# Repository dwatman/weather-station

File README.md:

# weather-station

Weather station with precision sensors, ZigBee connectivity to Home Assistant.

## Wireless Module
STM32WBA5MMG Wireless Module

## Sensors

| Type         | Part           | Accuracy          | Interface   | Voltage       | Current | Response |
| ------------ | -------------- | ----------------- | ----------- | ------------- | ------- | -------- |
| Temperature  | SHT45-AD1F | ± 0.1°C           | I²C         | 1.08 - 3.6 V  | 0.4 uA  | 4 s      |
| Humidity     | SHT45-AD1F | ± 1% RH           | I²C         | 1.08 - 3.6 V  | 0.4 uA  | 4 s      |
| Pressure     | LPS22DF    | ± 0.2 hPa         | I²C/SPI/I3C | 1.7 - 3.6 V   | 9 uA    | fast     |
| CO₂          | SCD41      | ±50.0 ppm + 2.5 % | I²C         | 2.4 - 5.5 V   | 15 mA   | 60 s     |
| VOC + NOx    | SGP41      | ± 15%?            | I²C         | 1.7 - 3.6 V   | 3 mA    | 10 s     |
| Particles    | SPS30      | ± 10%             | I²C/UART    | 4.5 - 5.5 V   | 55 mA   |          |
| Light        | OPT4001    | ± 2%              | I²C         | 1.6 - 3.6 V   | 30 µA   | <0.8 s   |
| Sound        | ICS-43434  | ± ?dB             | I²S         | 1.65 - 3.63 V | 490 µA  |          |
| Acceleration | LIS2HH12   | ± 0.1%            | I²C/SPI     | 1.71 - 3.6 V  | 180 µA  |          |
| IR Rx        | TSOP38436  | N/A               | Digital     | 2.0 - 5.5 V   | 450 µA  |          |

## Indoor Sensor Unit
* ZigBee for communication
* USB powered

### Sensors
* Temperature
* Humidity
* CO2
* VOC + NOx
* Particles
* Light
* IR remote control

## Outdoor Sensor Unit
* ZigBee for communication
* Solar + battery powered
* ~0.5 - 1W solar panel
* 18650 lithium cell for energy storage
* BQ25570 for solar/charge control

### Sensors
* Temperature
* Humidity
* Pressure
* Light (+UV?)
* Sound
* Battery level

## Display Unit
* WiFi for communication
* STM32H???

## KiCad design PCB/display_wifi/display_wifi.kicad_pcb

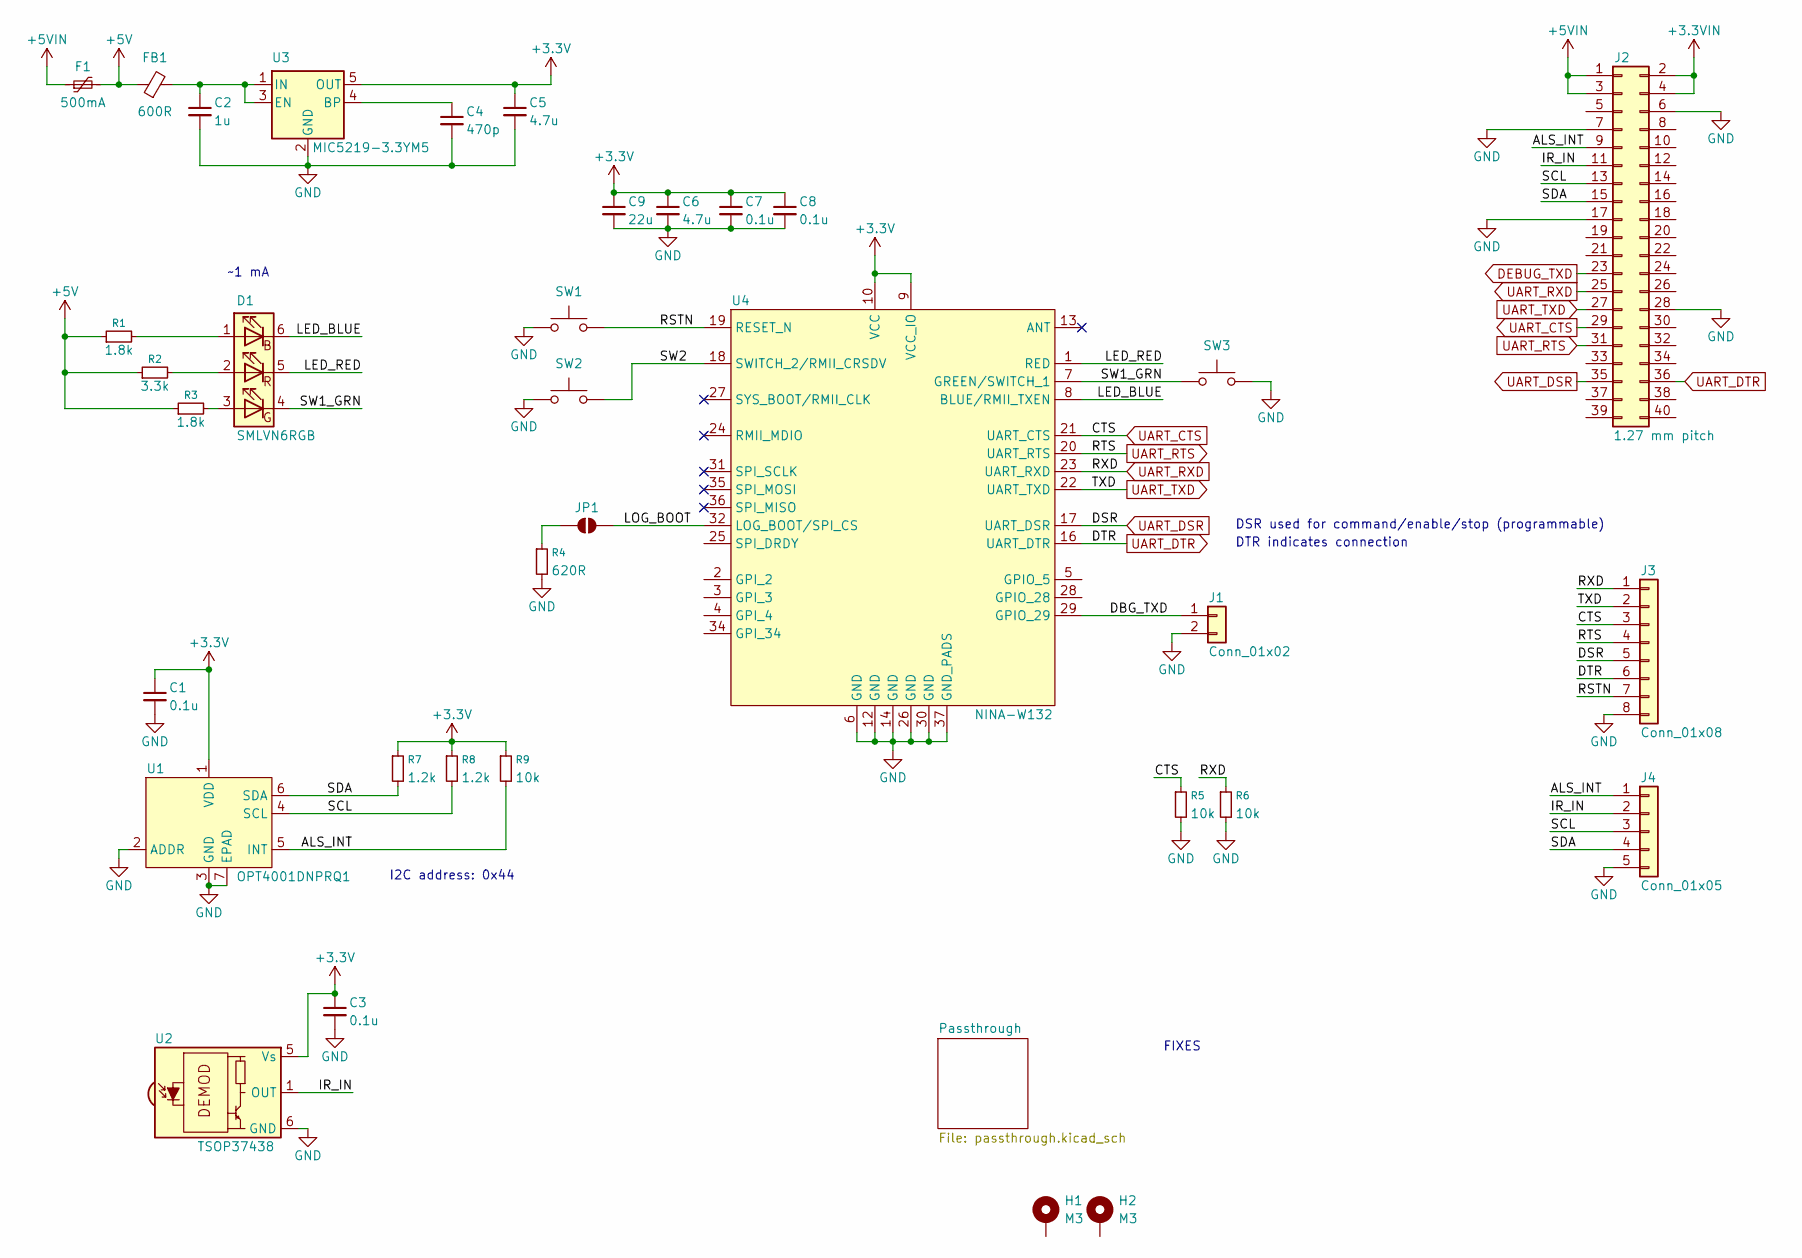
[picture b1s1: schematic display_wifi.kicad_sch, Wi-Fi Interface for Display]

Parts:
C1, C3, C7, C8: 0.1u; C_0402_1005Metric; MPN CL05B104KA5NNNC; Mouser PN 187-CL05B104KA5NNNC
C2: 1u; C_0402_1005Metric; MPN CL05A105KA5NQNC; Mouser PN 187-CL05A105KA5NQNC
C4: 470p; C_0402_1005Metric; MPN GRM1555C2A471JE01D; Mouser PN 81-GRM1555C2A471JE1D
C5, C6: 4.7u; C_0603_1608Metric; MPN CL10A475KO8NNNC; Mouser PN 187-CL10A475KO8NNNC
C9: 22u; C_1210_3225Metric
D1: SMLVN6RGB; LED_ROHM_SMLVN6; MPN SMLVN6RGB7W1; Mouser PN 755-SMLVN6RGB7W1
F1: 500mA; Fuse_1206_3216Metric; MPN MF-NSMF050-2; Mouser PN 652-MF-NSMF050-2
FB1: 600R; L_0805_2012Metric; MPN BLM21SP601SZ1D; Mouser PN 81-BLM21SP601SZ1D
H1, H2: M3; MountingHole_3.2mm_M3_Pad
J1: Conn_01x02; PinHeader_1x02_P2.54mm_Vertical
J2: 1.27 mm pitch; PinSocket_2x20_P1.27mm_Vertical; MPN 20021311-00040T4LF; Mouser PN 649-221311-00040T4LF
J3: Conn_01x08; PinHeader_1x08_P2.54mm_Vertical
J4: Conn_01x05; PinHeader_1x05_P2.54mm_Vertical
JP1: SolderJumper_2_Open; SolderJumper-2_P1.3mm_Open_TrianglePad1.0x1.5mm
R1, R3: 1.8k; R_0603_1608Metric
R2: 3.3k; R_0603_1608Metric
R4: 620R; R_0603_1608Metric
R5, R6, R9: 10k; R_0603_1608Metric
R7, R8: 1.2k; R_0603_1608Metric
SW1, SW2, SW3: TL3305; SW_Push_1P1T_NO_E-Switch_TL3305AFxxxQG; MPN TL3305BF100QG; Mouser PN 612-TL3305BF100QG
U1: OPT4001DNPRQ1; TI_USON-6-1EP_2x2mm_P0.5mm_EP0.65x1.35mm; MPN OPT4001DNPRQ1; Mouser PN 595-OPT4001DNPRQ1
U2: TSOP37438; Vishay_BELOBOG-4Pin; MPN TSOP37438TT1; Mouser PN 78-TSOP37438TT1
U3: MIC5219-3.3YM5; SOT-23-5; MPN MIC5219-3.3YM5-TR; Mouser PN 998-MIC5219-3.3YM5TR
U4: NINA-W132; ublox_NINA-W1x2; MPN NINA-W132-03B; Mouser PN 377-NINA-W132-03B

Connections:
+3.3V: C1.1, C3.1, C5.1, C6.1, C7.1, C8.1, C9.1, R7.1, R8.1, R9.1, U1.1 (VDD), U2.5 (Vs), U3.5 (OUT), U4.9 (VCC_IO), U4.10 (VCC)
+3.3VIN: J2.2, J2.4
+5V: F1.2, FB1.1, R1.1, R2.1, R3.1
+5VIN: F1.1, J2.1, J2.3
/ALS_INT: J2.9, J4.1, R9.2, U1.5 (INT)
/DBG_TXD: J1.1, U4.29 (GPIO_29)
/IR_IN: J2.11, J4.2, U2.1 (OUT)
/LED_BLUE: D1.6 (BK), U4.8 (BLUE/RMII_TXEN)
/LED_RED: D1.5 (RK), U4.1 (RED)
/LOG_BOOT: JP1.2 (B), U4.32 (LOG_BOOT/SPI_CS)
/RSTN: J3.7, SW1.2, U4.19 (RESET_N)
/SCL: J2.13, J4.3, R8.2, U1.4 (SCL)
/SDA: J2.15, J4.4, R7.2, U1.6 (SDA)
/SW1_GRN: D1.4 (GK), SW3.1, U4.7 (GREEN/SWITCH_1)
/SW2: SW2.2, U4.18 (SWITCH_2/RMII_CRSDV)
DEBUG_TXD: J2.23; also elsewhere on the board
GND: C1.2, C2.2, C3.2, C4.2, C5.2, C6.2, C7.2, C8.2, C9.2, J1.2, J2.6, J2.7, J2.17, J2.28, J3.8, J4.5, R4.2, R5.2, R6.2, SW1.1, SW2.1, SW3.2, U1.2 (ADDR), U1.3 (GND), U1.7 (EPAD), U2.6 (GND), U2.8 (GND), U3.2 (GND), U4.6 (GND), U4.12 (GND), U4.14 (GND), U4.26 (GND), U4.30 (GND), U4.37 (GND_PADS); also elsewhere on the board
unnamed: D1.1 (BA), R1.2
unnamed: D1.3 (GA), R3.2
unnamed: D1.2 (RA), R2.2
unnamed: JP1.1 (A), R4.1
unnamed: C4.1, U3.4 (BP)
unnamed: C2.1, FB1.2, U3.1 (IN), U3.3 (EN)
UART_CTS: J2.29, J3.3, R5.1, U4.21 (UART_CTS)
UART_DSR: J2.35, J3.5, U4.17 (UART_DSR)
UART_DTR: J2.36, J3.6, U4.16 (UART_DTR)
UART_RTS: J2.31, J3.4, U4.20 (UART_RTS)
UART_RXD: J2.25, J3.1, R6.1, U4.23 (UART_RXD)
UART_TXD: J2.27, J3.2, U4.22 (UART_TXD)

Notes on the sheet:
DTR indicates connection
DSR used for command/enable/stop (programmable)
I2C address: 0x44
~1 mA
FIXES

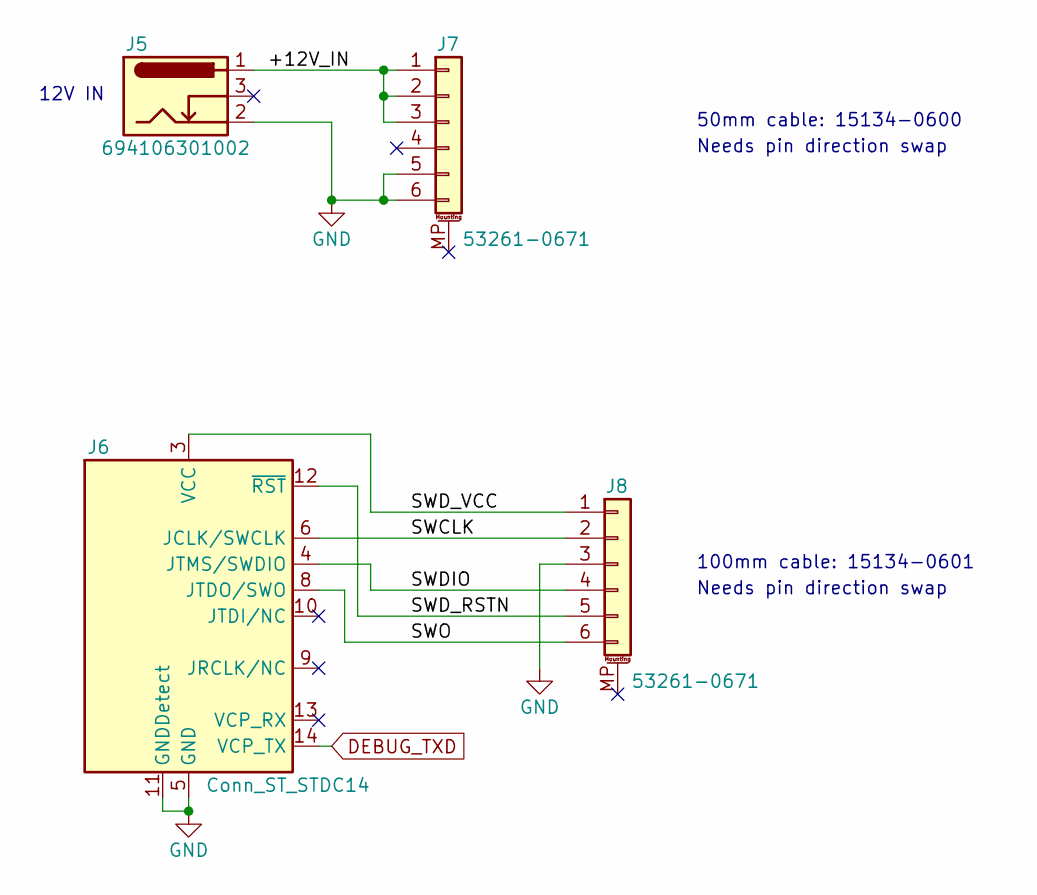
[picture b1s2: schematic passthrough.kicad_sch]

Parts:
J5: 694106301002; BarrelJack_Wuerth_6941xx301002; MPN 694106301002; Mouser PN 710-694106301002
J6: Conn_ST_STDC14; PinHeader_2x07_P1.27mm_Vertical; MPN 20021111-00014T1LF; Mouser PN 649-200211110014T1LF
J7, J8: 53261-0671; Molex_PicoBlade_53261-0671_1x06-1MP_P1.25mm_Horizontal; MPN 53261-0671; Mouser PN 538-53261-0671

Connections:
/Passthrough/+12V_IN: J5.1, J7.1, J7.2, J7.3
/Passthrough/SWCLK: J6.6 (JCLK/SWCLK), J8.2
/Passthrough/SWDIO: J6.4 (JTMS/SWDIO), J8.4
/Passthrough/SWD_RSTN: J6.12 (~RST), J8.5
/Passthrough/SWD_VCC: J6.3 (VCC), J8.1
/Passthrough/SWO: J6.8 (JTDO/SWO), J8.6
DEBUG_TXD: J6.14 (VCP_TX); also elsewhere on the board
GND: J5.2, J6.5 (GND), J6.7 (GND), J6.11 (GNDDetect), J7.5, J7.6, J8.3; also elsewhere on the board

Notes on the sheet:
50mm cable: 15134-0600
Needs pin direction swap
100mm cable: 15134-0601
12V IN

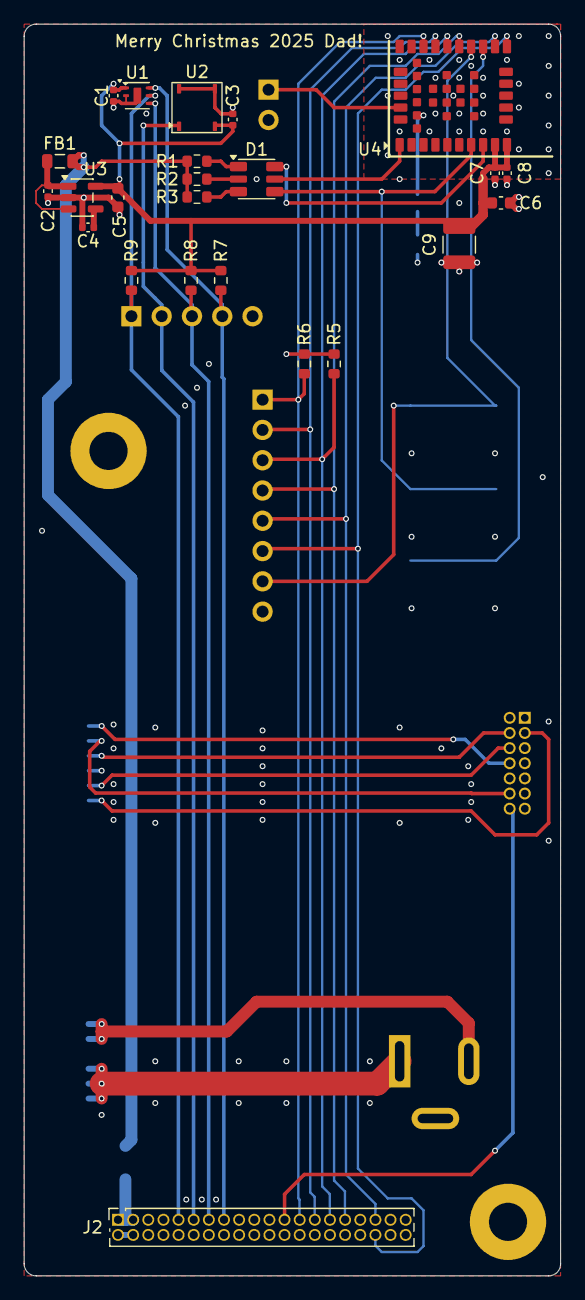
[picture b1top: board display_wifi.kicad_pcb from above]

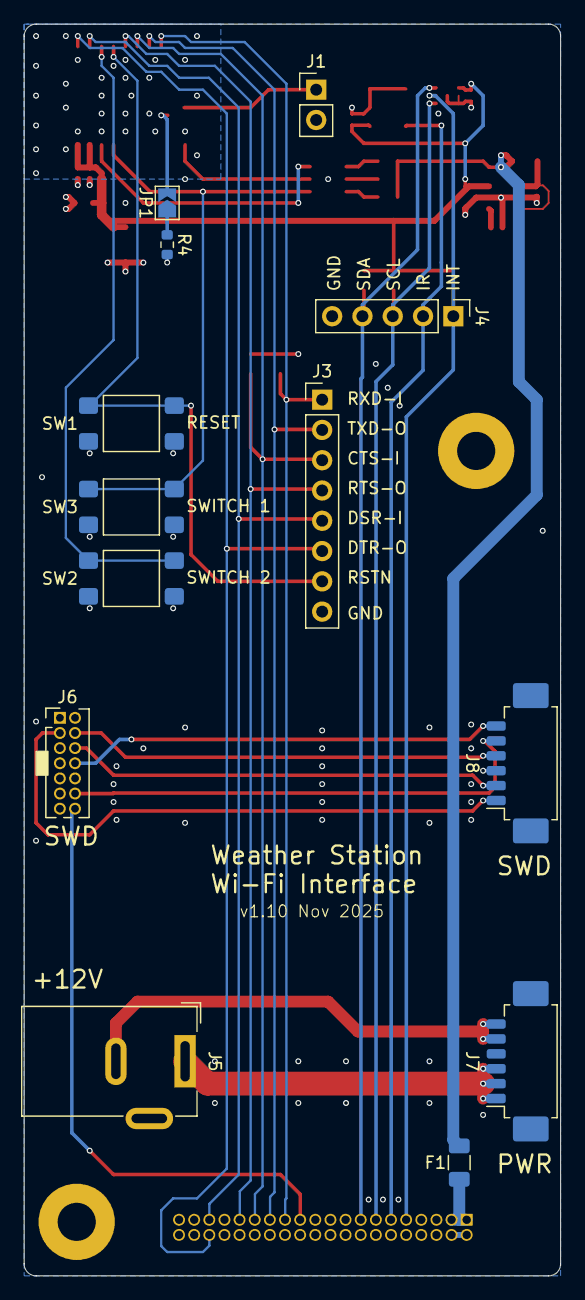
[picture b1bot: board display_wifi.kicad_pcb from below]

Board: 2 copper layers, 45.0 x 105.0 mm, 39 parts (13 on the bottom side), 35 nets.

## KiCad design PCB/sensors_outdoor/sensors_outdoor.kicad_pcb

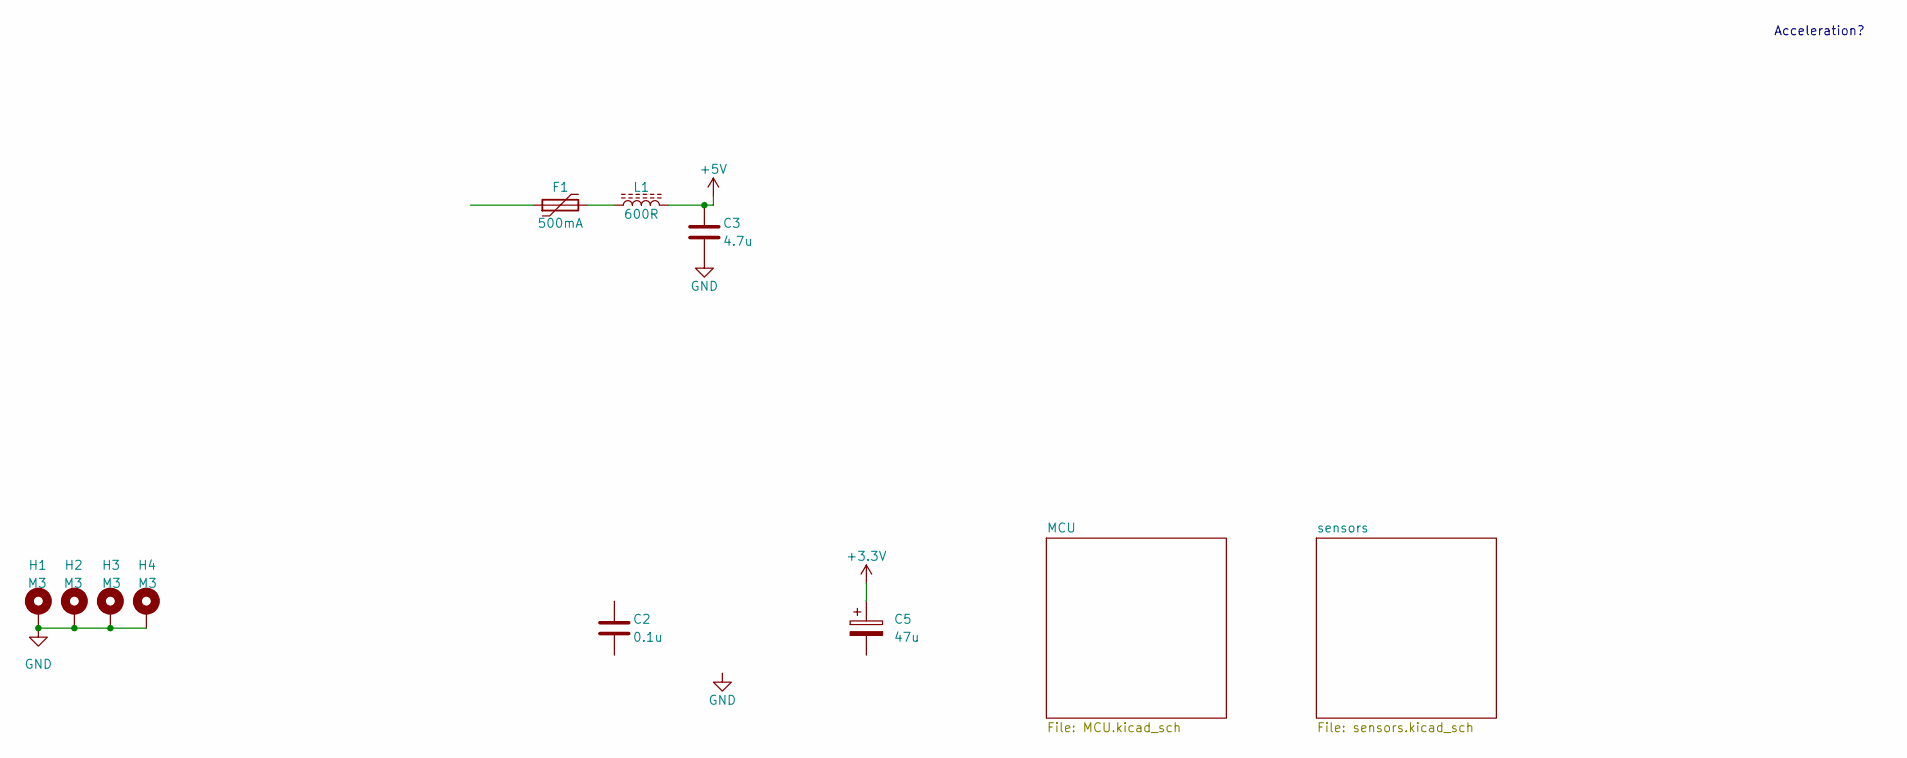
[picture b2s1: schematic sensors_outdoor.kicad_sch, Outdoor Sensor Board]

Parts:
C2: 0.1u; C_0402_1005Metric
C3: 4.7u; C_0805_2012Metric
C5: 47u; CP_EIA-7343-31_Kemet-D; MPN T491D476K010AT; Mouser PN 80-T491D476K010
F1: 500mA; Fuse_0805_2012Metric
H1, H2, H3, H4: M3; MountingHole_3.2mm_M3_Pad
L1: 600R; L_0805_2012Metric; MPN HZ0805E601R-10; Mouser PN 875-HZ0805E601R-10

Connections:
+3.3V: C5.1; also elsewhere on the board
+5V: C3.1, L1.2
GND: C3.2, H1.1, H2.1, H3.1, H4.1; also elsewhere on the board
unnamed: F1.2, L1.1

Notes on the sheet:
Acceleration?

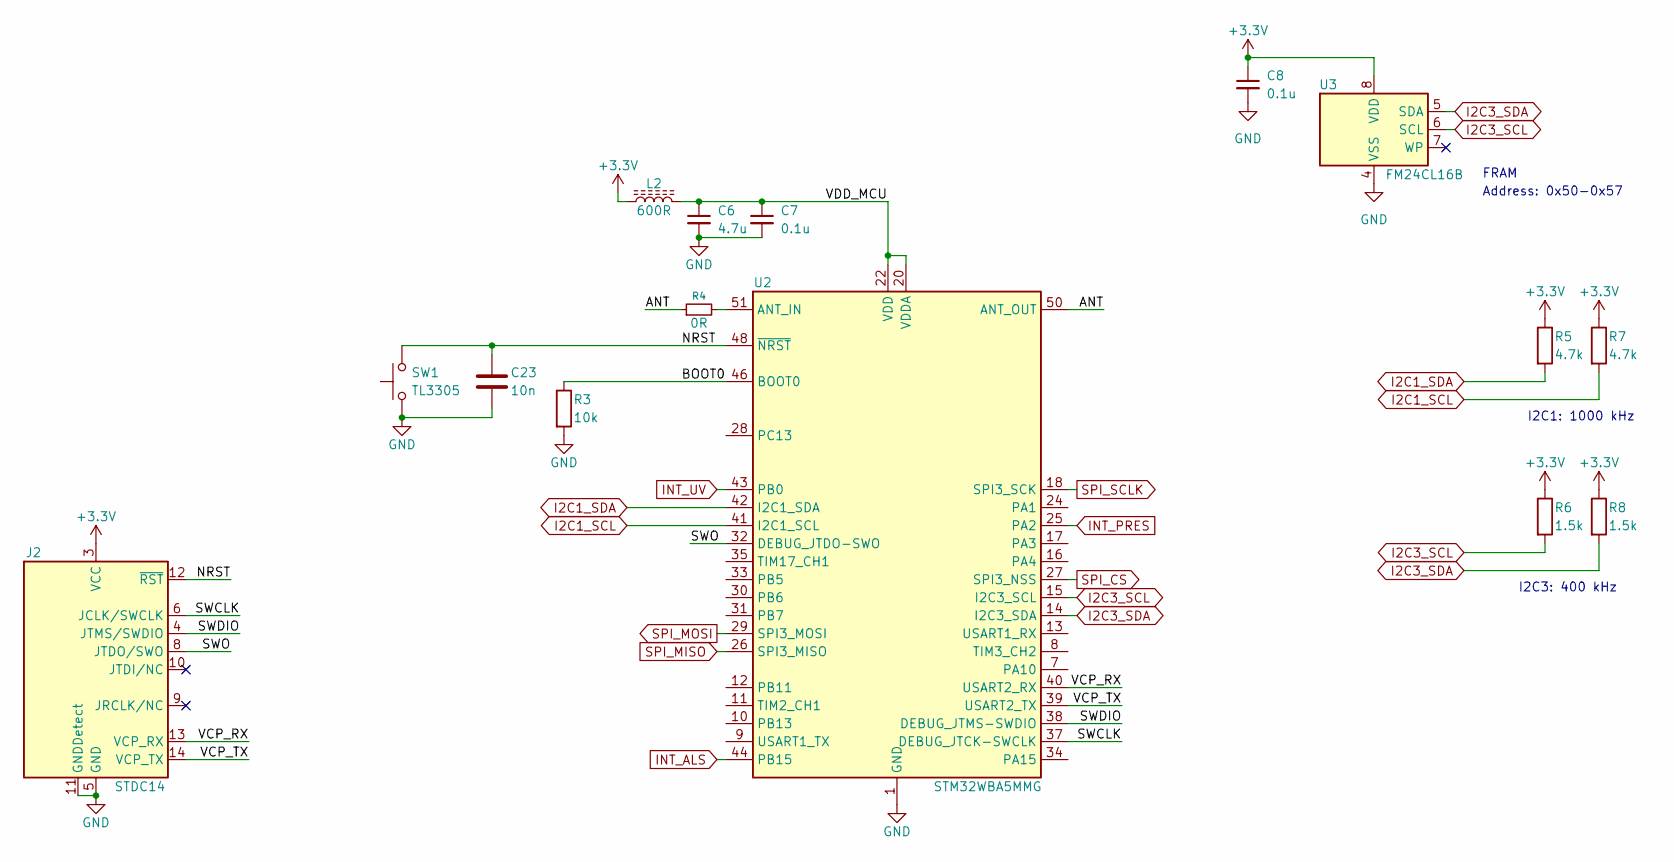
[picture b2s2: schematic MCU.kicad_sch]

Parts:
C6: 4.7u; C_0805_2012Metric
C7, C8: 0.1u; C_0402_1005Metric
C23: 10n; C_0402_1005Metric
J2: STDC14; SAMTEC_FTSH-107-01-L-DV-K-A; MPN FTSH-107-01-L-DV-K-A; Mouser PN 200-FTSH10701LDVKA
L2: 600R; L_0805_2012Metric; MPN HZ0805E601R-10; Mouser PN 875-HZ0805E601R-10
R3: 10k; R_0603_1608Metric
R4: 0R; R_0402_1005Metric
R5, R7: 4.7k; R_0603_1608Metric
R6, R8: 1.5k; R_0603_1608Metric
SW1: TL3305; SW_Push_1P1T_NO_E-Switch_TL3305AFxxxQG; MPN TL3305AF260QG; Mouser PN 612-TL3305AF260QG
U2: STM32WBA5MMG; MPN STM32WBA5MMGH6TR; Mouser PN 511-STM32WBA5MMGH6TR
U3: FM24CL16B; SOIC-8_3.9x4.9mm_P1.27mm; MPN FM24CL16B-G; Mouser PN 877-FM24CL16B-G

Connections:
+3.3V: C8.1, J2.3 (VCC), L2.1, R5.1, R6.1, R7.1, R8.1, U3.8 (VDD); also elsewhere on the board
/MCU/ANT: R4.1, U2.50 (ANT_OUT)
/MCU/BOOT0: R3.1, U2.46 (BOOT0)
/MCU/NRST: C23.1, J2.12 (~RST), SW1.2, U2.48 (~NRST)
/MCU/SWCLK: J2.6 (JCLK/SWCLK), U2.37 (DEBUG_JTCK-SWCLK)
/MCU/SWDIO: J2.4 (JTMS/SWDIO), U2.38 (DEBUG_JTMS-SWDIO)
/MCU/SWO: J2.8 (JTDO/SWO), U2.32 (DEBUG_JTDO-SWO)
/MCU/VCP_RX: J2.13 (VCP_RX), U2.40 (USART2_RX)
/MCU/VCP_TX: J2.14 (VCP_TX), U2.39 (USART2_TX)
/MCU/VDD_MCU: C6.1, C7.1, L2.2, U2.20 (VDDA), U2.22 (VDD)
GND: C6.2, C7.2, C8.2, C23.2, J2.5 (GND), J2.7 (GND), J2.11 (GNDDetect), R3.2, SW1.1, U2.1 (GND), U2.6 (GND), U2.19 (GND), U2.21 (GND), U2.23 (GND), U2.36 (GND), U2.45 (GND), U2.47 (GND), U2.49 (GND), U2.52 (GND), U2.53 (GND), U2.54 (GND), U2.55 (GND), U2.57 (GND), U2.58 (GND), U2.60 (GND), U2.61 (GND), U2.62 (GND), U2.63 (GND), U2.64 (GND), U2.65 (GND), U2.66 (GND), U2.67 (GND), U2.68 (GND), U2.69 (GND), U2.70 (GND), U2.71 (GND), U2.72 (GND), U2.73 (GND), U2.74 (GND), U2.75 (GND), U2.76 (GND), U3.4 (VSS); also elsewhere on the board
I2C1_SCL: R7.2, U2.41 (I2C1_SCL); also elsewhere on the board
I2C1_SDA: R5.2, U2.42 (I2C1_SDA); also elsewhere on the board
I2C3_SCL: R6.2, U2.15 (I2C3_SCL), U3.6 (SCL)
I2C3_SDA: R8.2, U2.14 (I2C3_SDA), U3.5 (SDA)
INT_ALS: U2.44 (PB15); also elsewhere on the board
INT_PRES: U2.25 (PA2); also elsewhere on the board
INT_UV: U2.43 (PB0); also elsewhere on the board
unnamed: R4.2, U2.51 (ANT_IN)
SPI_CS: U2.27 (SPI3_NSS); also elsewhere on the board
SPI_MISO: U2.26 (SPI3_MISO); also elsewhere on the board
SPI_MOSI: U2.29 (SPI3_MOSI); also elsewhere on the board
SPI_SCLK: U2.18 (SPI3_SCK); also elsewhere on the board

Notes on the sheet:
I2C3: 400 kHz
Address: 0x50-0x57
I2C1: 1000 kHz
FRAM

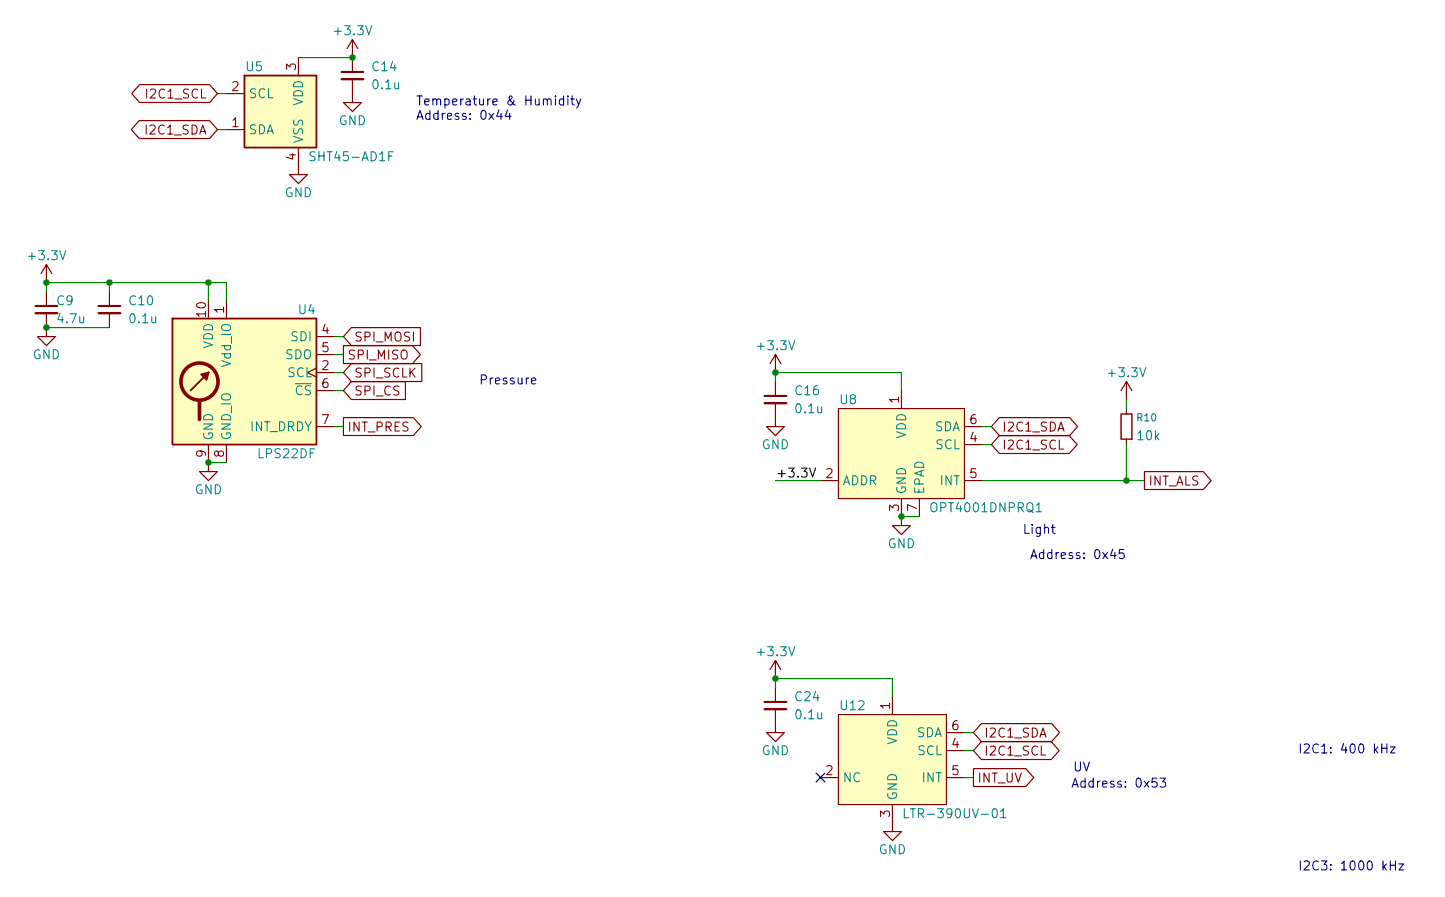
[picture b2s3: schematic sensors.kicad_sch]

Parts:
C9: 4.7u; C_0805_2012Metric
C10, C14, C16, C24: 0.1u; C_0402_1005Metric
R10: 10k; R_0603_1608Metric
U4: LPS22DF; ST_HLGA-10L_2x2mm_P0.5mm_LayoutBorder3x2y; MPN LPS22DFTR; Mouser PN 511-LPS22DFTR
U5: SHT45-AD1F; Sensirion_DFN-4_1.5x1.5mm_P0.8mm_SHT4x_NoCentralPad; MPN SHT45-AD1F-R2; Mouser PN 403-SHT45-AD1F-R2
U8: OPT4001DNPRQ1; TI_USON-6-1EP_2x2mm_P0.5mm_EP0.65x1.35mm; MPN OPT4001DNPRQ1; Mouser PN 595-OPT4001DNPRQ1
U12: LTR-390UV-01; Liteon_LTR-390UV-01; MPN LTR-390UV-01; Mouser PN 859-LTR390UV01

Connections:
+3.3V: C9.1, C10.1, C14.1, C16.1, C24.1, R10.2, U4.1 (Vdd_IO), U4.10 (VDD), U5.3 (VDD), U8.1 (VDD), U8.2 (ADDR), U12.1 (VDD); also elsewhere on the board
GND: C9.2, C10.2, C14.2, C16.2, C24.2, U4.3 (GND), U4.8 (GND_IO), U4.9 (GND), U5.4 (VSS), U8.3 (GND), U8.7 (EPAD), U12.3 (GND); also elsewhere on the board
I2C1_SCL: U5.2 (SCL), U8.4 (SCL), U12.4 (SCL); also elsewhere on the board
I2C1_SDA: U5.1 (SDA), U8.6 (SDA), U12.6 (SDA); also elsewhere on the board
INT_ALS: R10.1, U8.5 (INT); also elsewhere on the board
INT_PRES: U4.7 (INT_DRDY); also elsewhere on the board
INT_UV: U12.5 (INT); also elsewhere on the board
SPI_CS: U4.6 (~CS); also elsewhere on the board
SPI_MISO: U4.5 (SDO); also elsewhere on the board
SPI_MOSI: U4.4 (SDI); also elsewhere on the board
SPI_SCLK: U4.2 (SCL); also elsewhere on the board

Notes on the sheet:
Address: 0x53
Address: 0x44
Light
Pressure
I2C1: 400 kHz
Address: 0x45
I2C3: 1000 kHz
Temperature & Humidity

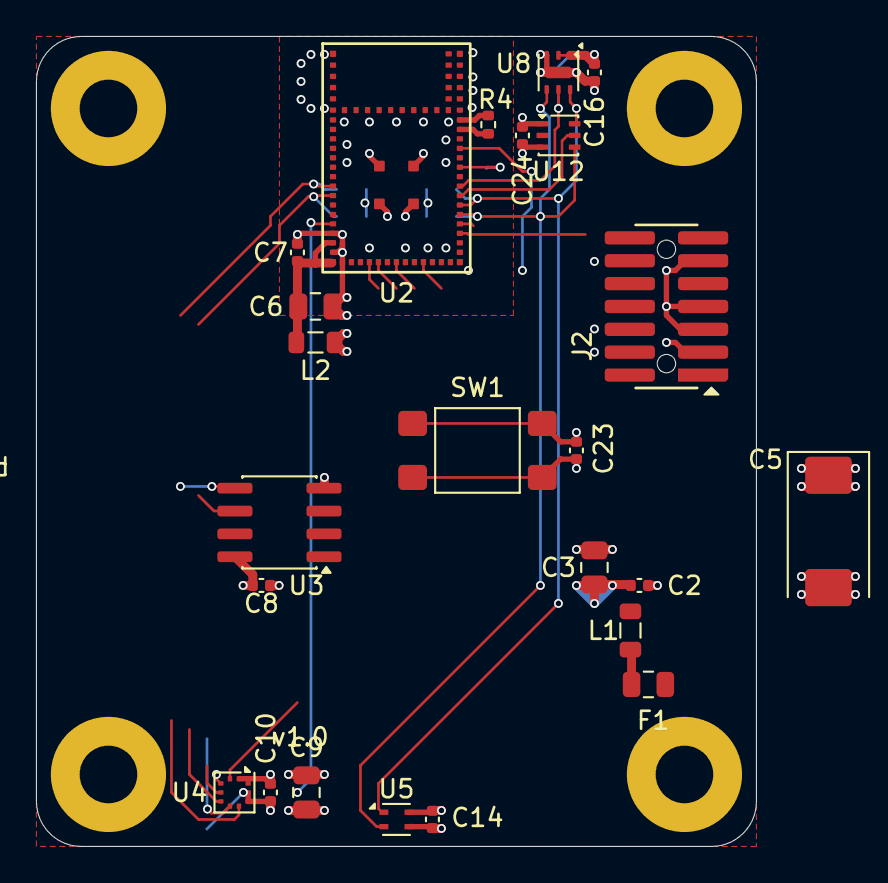
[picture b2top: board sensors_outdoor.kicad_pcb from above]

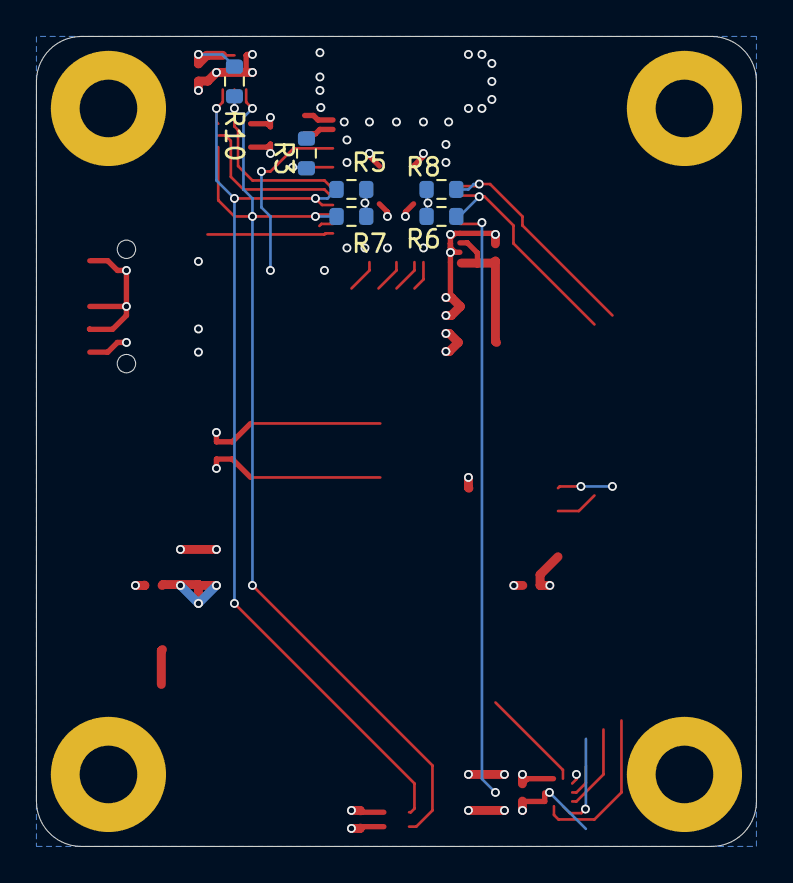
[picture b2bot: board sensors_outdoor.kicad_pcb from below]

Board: 4 copper layers, 40.0 x 45.0 mm, 34 parts (6 on the bottom side), 25 nets.

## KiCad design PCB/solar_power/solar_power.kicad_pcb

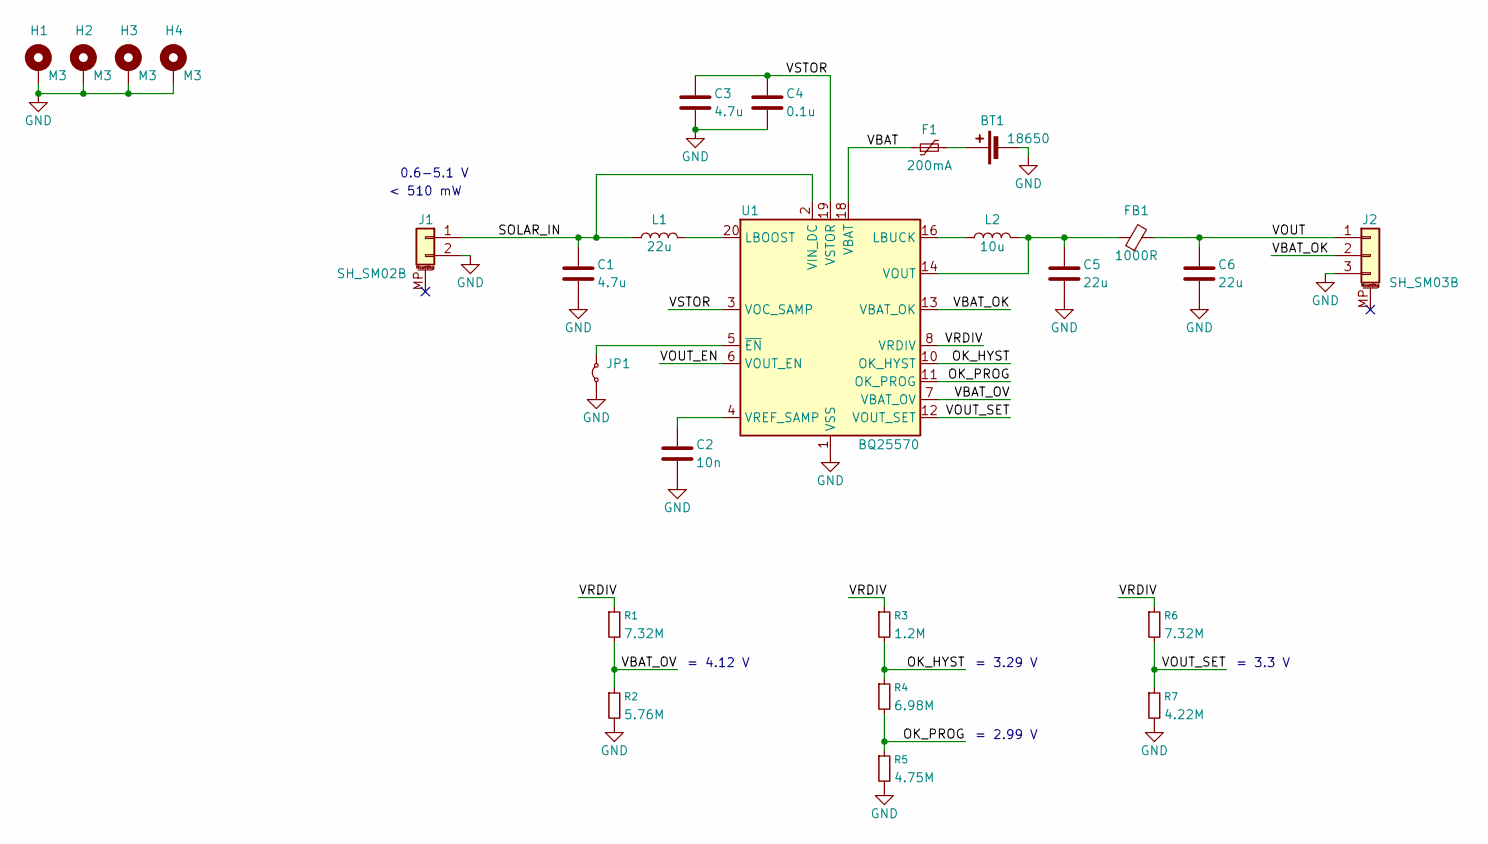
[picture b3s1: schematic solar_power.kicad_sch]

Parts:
BT1: 18650; Keystone_1043P_1x18650; MPN 1043P; Mouser PN 534-1043P
C1, C3: 4.7u; C_0805_2012Metric
C2: 10n; C_0402_1005Metric
C4: 0.1u; C_0402_1005Metric
C5, C6: 22u; C_0805_2012Metric; MPN CL21A226MAYNNNE; Mouser PN 187-CL21A226MAYNNNE
F1: 200mA; Fuse_1206_3216Metric; MPN 0ZCJ0020FF2E; Mouser PN 530-0ZCJ0020FF2E
FB1: 1000R; L_0603_1608Metric; MPN BLM18AG102SN1D; Mouser PN 81-BLM11A102S
H1, H2, H3, H4: M3; MountingHole_3.2mm_M3_Pad
J1: SH_SM02B; JST_SH_SM02B-SRSS-TB_1x02-1MP_P1.00mm_Horizontal; MPN SM02B-SRSS-TB(LF)(SN); Mouser PN 306-SM02BSRSSTBLFSN
J2: SH_SM03B; JST_SH_SM03B-SRSS-TB_1x03-1MP_P1.00mm_Horizontal; MPN SM03B-SRSS-TB(LF)(SN); Mouser PN 306-SM03BSRSSTBLFSNP
JP1: Jumper_2_Small_Bridged; SolderJumper-2_P1.3mm_Open_TrianglePad1.0x1.5mm
L1: 22u; L_Abracon_ASPI-4030S; MPN ASPI-4030S-220M-T; Mouser PN 815-ASPI-4030S-220MT
L2: 10u; L_Abracon_ASPI-3012S; MPN ASPI-3012S-100M-T; Mouser PN 815-ASPI-3012S-100MT
R1, R6: 7.32M; R_0805_2012Metric; MPN RC0805FR-077M32L; Mouser PN 603-RC0805FR-077M32L
R2: 5.76M; R_0805_2012Metric; MPN RC0805FR-075M76L; Mouser PN 603-RC0805FR-075M76L
R3: 1.2M; R_0805_2012Metric; MPN RC0805FR-101M2L; Mouser PN 603-RC0805FR-101M2L
R4: 6.98M; R_0805_2012Metric; MPN RC0805FR-076M98L; Mouser PN 603-RC0805FR-076M98L
R5: 4.75M; R_0805_2012Metric; MPN RC0805FR-074M75L; Mouser PN 603-RC0805FR-074M75L
R7: 4.22M; R_0805_2012Metric; MPN RC0805FR-074M22L; Mouser PN 603-RC0805FR-074M22L
U1: BQ25570; QFN-20-1EP_3.5x3.5mm_P0.5mm_EP2x2mm; MPN BQ25570RGRR; Mouser PN 595-BQ25570RGRR

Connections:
/OK_HYST: R3.2, R4.1, U1.10 (OK_HYST)
/OK_PROG: R4.2, R5.1, U1.11 (OK_PROG)
/SOLAR_IN: C1.1, J1.1, L1.1, U1.2 (VIN_DC)
/VBAT: F1.1, U1.18 (VBAT)
/VBAT_OK: J2.2, U1.13 (VBAT_OK)
/VBAT_OV: R1.2, R2.1, U1.7 (VBAT_OV)
/VOUT: C6.1, FB1.2, J2.1
/VOUT_EN: U1.6 (VOUT_EN)
/VOUT_SET: R6.2, R7.1, U1.12 (VOUT_SET)
/VRDIV: R1.1, R3.1, R6.1, U1.8 (VRDIV)
/VSTOR: C3.1, C4.1, U1.3 (VOC_SAMP), U1.19 (VSTOR)
GND: BT1.2 (-), C1.2, C2.2, C3.2, C4.2, C5.2, C6.2, H1.1, H2.1, H3.1, H4.1, J1.2, J2.3, JP1.1 (A), R2.2, R5.2, R7.2, U1.1 (VSS), U1.9 (VSS), U1.15 (VSS), U1.17 (VSS), U1.21 (VSS)
unnamed: BT1.1 (+), F1.2
unnamed: JP1.2 (B), U1.5 (~EN)
unnamed: L1.2, U1.20 (LBOOST)
unnamed: L2.1, U1.16 (LBUCK)
unnamed: C5.1, FB1.1, L2.2, U1.14 (VOUT)
unnamed: C2.1, U1.4 (VREF_SAMP)

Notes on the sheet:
= 2.99 V
0.6-5.1 V
= 3.3 V
= 3.29 V
= 4.12 V
< 510 mW

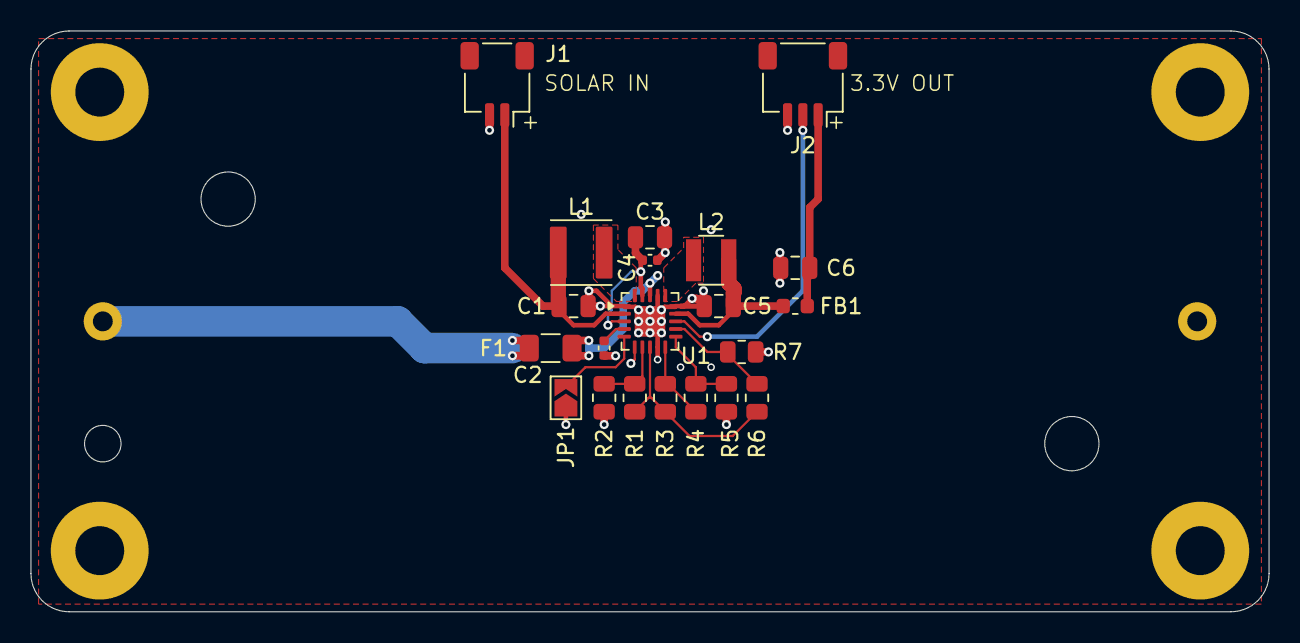
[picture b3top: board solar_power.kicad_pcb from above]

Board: 2 copper layers, 81.0 x 38.0 mm, 26 parts (1 on the bottom side), 17 nets.

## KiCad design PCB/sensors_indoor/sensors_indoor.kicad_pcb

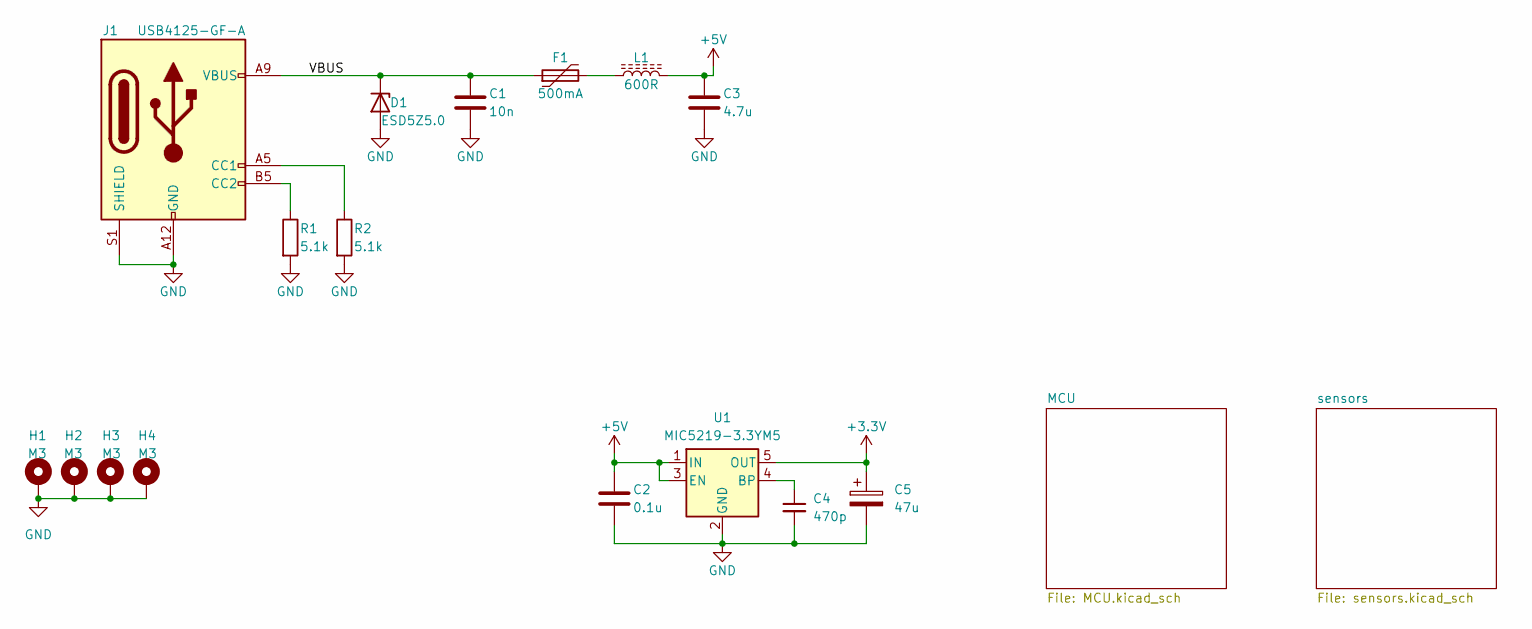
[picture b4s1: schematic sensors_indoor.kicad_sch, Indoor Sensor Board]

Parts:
C1: 10n; C_0402_1005Metric
C2: 0.1u; C_0402_1005Metric
C3: 4.7u; C_0805_2012Metric
C4: 470p; C_0402_1005Metric
C5: 47u; CP_EIA-7343-31_Kemet-D; MPN T491D476K010AT; Mouser PN 80-T491D476K010
D1: ESD5Z5.0; D_SOD-523; MPN ESD5Z5.0T1G; Mouser PN 863-ESD5Z5.0T1G
F1: 500mA; Fuse_1206_3216Metric; MPN MF-NSMF050-2; Mouser PN 652-MF-NSMF050-2
H1, H2, H3, H4: M3; MountingHole_3.2mm_M3_Pad
J1: USB4125-GF-A; USB_C_Receptacle_GCT_USB4125-xx-x-0190_6P_TopMnt_Horizontal; MPN USB4125-GF-A; Mouser PN 640-USB4125-GF-A
L1: 600R; L_0805_2012Metric; MPN HZ0805E601R-10; Mouser PN 875-HZ0805E601R-10
R1, R2: 5.1k; R_0603_1608Metric
U1: MIC5219-3.3YM5; SOT-23-5; MPN MIC5219-3.3YM5-TR; Mouser PN 998-MIC5219-3.3YM5TR

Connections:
+3.3V: C5.1, U1.5 (OUT); also elsewhere on the board
+5V: C2.1, C3.1, L1.2, U1.1 (IN), U1.3 (EN); also elsewhere on the board
/VBUS: C1.1, D1.1 (K), F1.1, J1.A9 (VBUS), J1.B9 (VBUS)
GND: C1.2, C2.2, C3.2, C4.2, C5.2, D1.2 (A), H1.1, H2.1, H3.1, H4.1, J1.A12 (GND), J1.B12 (GND), J1.S1 (SHIELD), R1.2, R2.2, U1.2 (GND); also elsewhere on the board
unnamed: F1.2, L1.1
unnamed: J1.A5 (CC1), R2.1
unnamed: J1.B5 (CC2), R1.1
unnamed: C4.1, U1.4 (BP)
